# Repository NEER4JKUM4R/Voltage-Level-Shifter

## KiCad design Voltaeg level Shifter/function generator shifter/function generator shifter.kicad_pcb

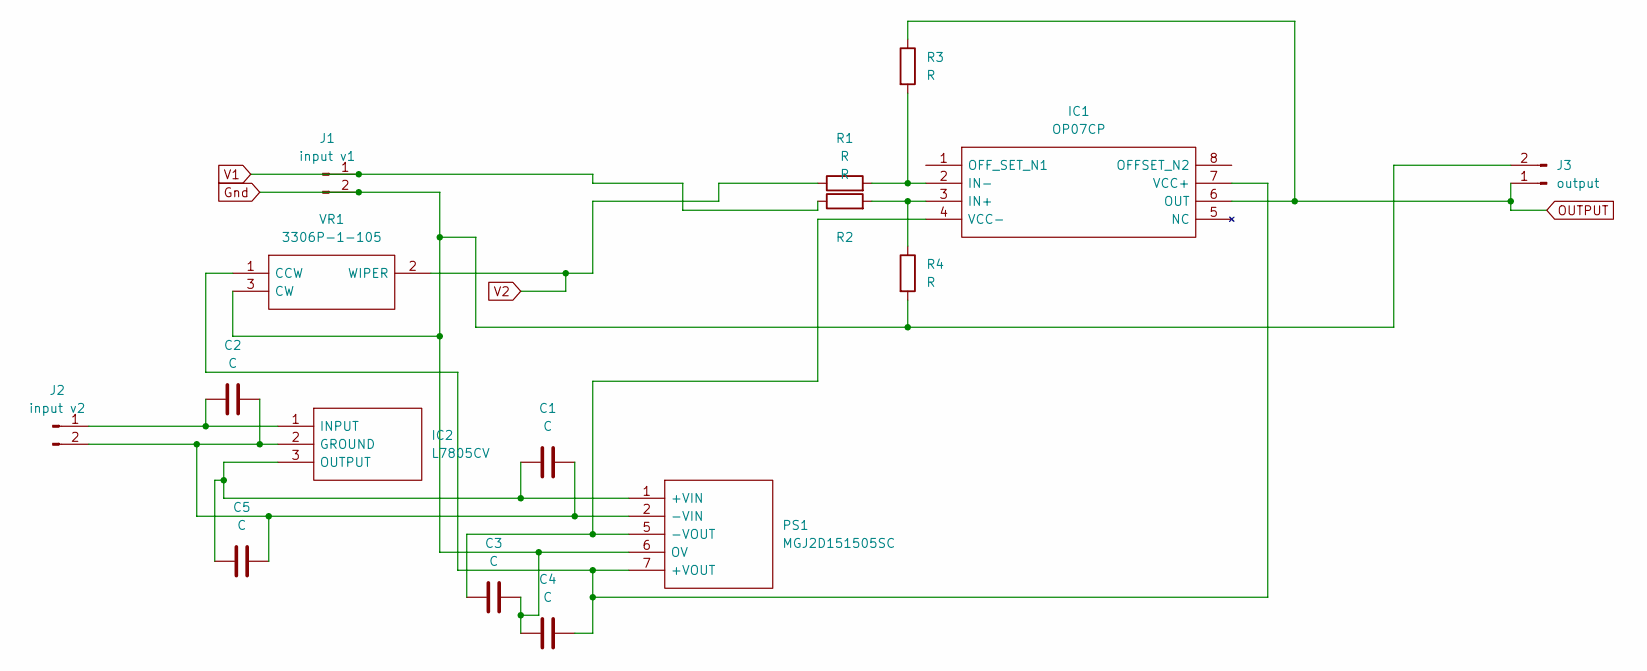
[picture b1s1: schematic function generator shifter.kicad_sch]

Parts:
C1, C2, C3, C4, C5: C; C_0805_2012Metric
IC1: OP07CP; DIP794W53P254L959H508Q8N; Manufacturer_Part_Number OP07CP; Mouser Part Number 595-OP07CP
IC2: L7805CV; TO255P460X1020X2008-3P; Manufacturer_Part_Number L7805CV; Mouser Part Number 511-L7805CV
J1: input v1; PinHeader_1x02_P2.54mm_Vertical
J2: input v2; PinHeader_1x02_P2.54mm_Vertical
J3: output; PinHeader_1x02_P2.54mm_Vertical
PS1: MGJ2D151505SC; Manufacturer_Part_Number MGJ2D151505SC; Mouser Part Number 580-MGJ2D151505SC
R1, R2, R3, R4: R; R_0805_2012Metric
VR1: 3306P-1-105; 3306P1105; Manufacturer_Part_Number 3306P-1-105; Mouser Part Number 652-3306P-1-105

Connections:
Gnd: C3.2, C4.1, J1.2, J3.2, PS1.6 (OV), R4.2, VR1.3 (CW)
unnamed: IC1.3 (IN+), R2.2, R4.1
unnamed: IC1.2 (IN-), R1.2, R3.2
unnamed: C4.2, IC1.7 (VCC+), PS1.7 (+VOUT), VR1.1 (CCW)
unnamed: C3.1, IC1.4 (VCC-), PS1.5 (-VOUT)
unnamed: C1.2, C2.2, C5.2, IC2.2 (GROUND), J2.2, PS1.2 (-VIN)
unnamed: C2.1, IC2.1 (INPUT), J2.1
unnamed: C1.1, C5.1, IC2.3 (OUTPUT), PS1.1 (+VIN)
OUTPUT: IC1.6 (OUT), J3.1, R3.1
V1: J1.1, R2.1
V2: R1.1, VR1.2 (WIPER)

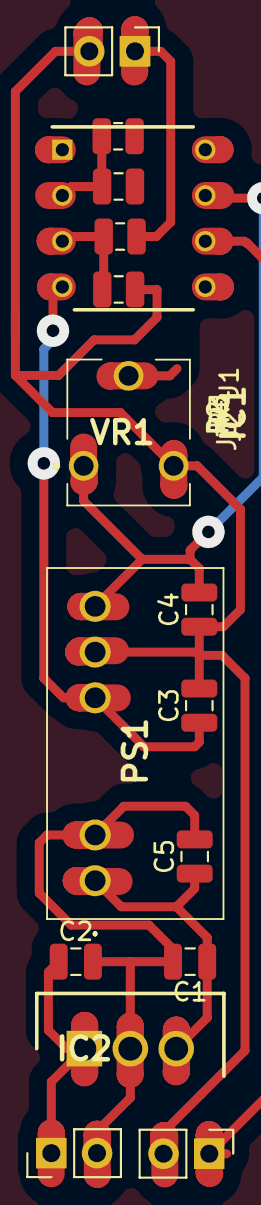
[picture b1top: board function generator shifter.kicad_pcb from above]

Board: 2 copper layers, 16 parts (0 on the bottom side), 11 nets.

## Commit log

2023-07-23 first comment
